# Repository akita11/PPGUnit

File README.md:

# PPG Clip

[M5Stack社の心拍センサユニット](https://www.switch-science.com/products/5695)と機能的に互換のUnitです。
光学脈波(PPG)センサのMAX30100を使用し、光学脈波やSpO2、そこから心拍数の計測ができます。
また[PPG Clip部品セット](https://github.com/akita11/PPGclip)と組み合わせることで、透過型PPG計測装置をつくることができます。

※センサICのMAX30100は、再生品を使用している場合があります。基本的な測定には問題がないことは確認済みですが、新品とは多少の性能の差異がある場合があります。

## 使い方

[M5Stack社の心拍センサユニット](https://www.switch-science.com/products/5695)と機能的に互換ですので、そちらのソフトウエア(Arduino用ライブラリ、UIFlow等)がそのまま使用できます。

## 作り方

2枚の基板を、向きをあわせて、2組の4pピンヘッダではんだ付けします。
ピンヘッダの足は十分に短くカットしてください。

## 補足情報(I2C信号線について)

MAX30100のI2C信号線の端子の絶対最大定格は6.0Vです。
I2C信号線のプルアップ抵抗はGroveコネクタのVDD側(M5Stackシリーズでは5V)に接続されており、HレベルはVDD電圧（同5V）となりますが、絶対最大定格を超えません。
M5Stack社の心拍センサユニットでは、ここに電圧変換用の部品が入っていますが、I2C信号の波形を観測したところ、立ち下がり速度がかなり遅く、特に400kHz通信の場合には通信エラーが多発する現象が確認されましたので、この構成としています。

## Author

Junichi Akita (@akita11) / akita@ifdl.jp

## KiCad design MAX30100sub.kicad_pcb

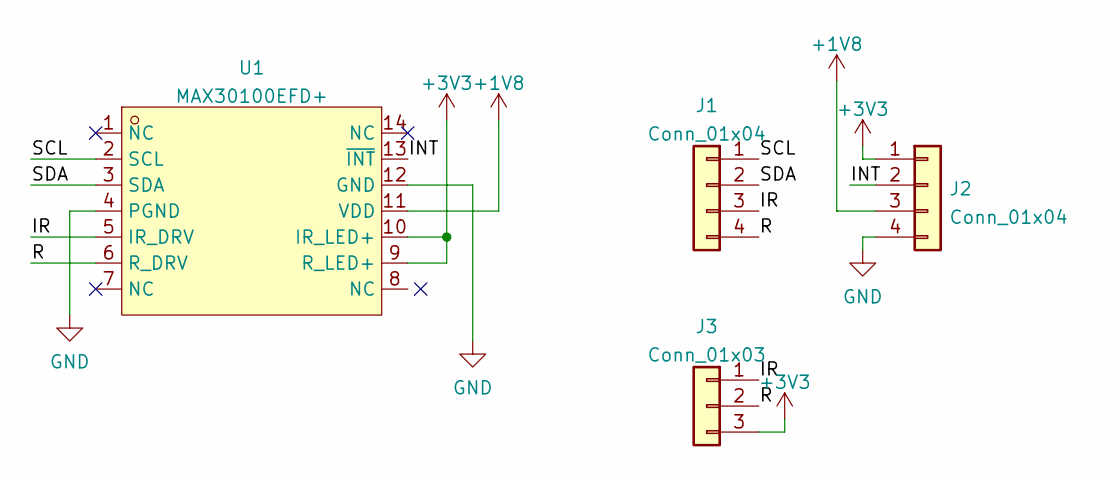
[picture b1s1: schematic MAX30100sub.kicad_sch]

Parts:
J1, J2: Conn_01x04; PinHeader_1x04_P2.54mm_Vertical
J3: Conn_01x03; PinSocket_1x03_P2.00mm_Vertical
U1: MAX30100EFD+; SENSOR-SMD_MAX30100EFD; LCSC Part C92512

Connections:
+1V8: J2.3, U1.11 (VDD)
+3V3: J2.1, J3.3, U1.9 (R_LED+), U1.10 (IR_LED+)
/INT: J2.2, U1.13 (~INT)
/IR: J1.3, J3.1, U1.5 (IR_DRV)
/R: J1.4, J3.2, U1.6 (R_DRV)
/SCL: J1.1, U1.2 (SCL)
/SDA: J1.2, U1.3 (SDA)
GND: J2.4, U1.4 (PGND), U1.12 (GND)

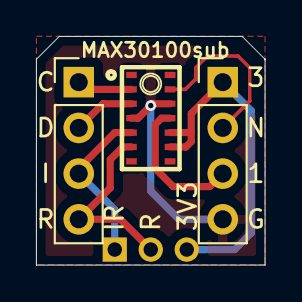
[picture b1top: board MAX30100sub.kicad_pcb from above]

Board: 2 copper layers, 12.7 x 12.7 mm, 4 parts (0 on the bottom side), 8 nets.

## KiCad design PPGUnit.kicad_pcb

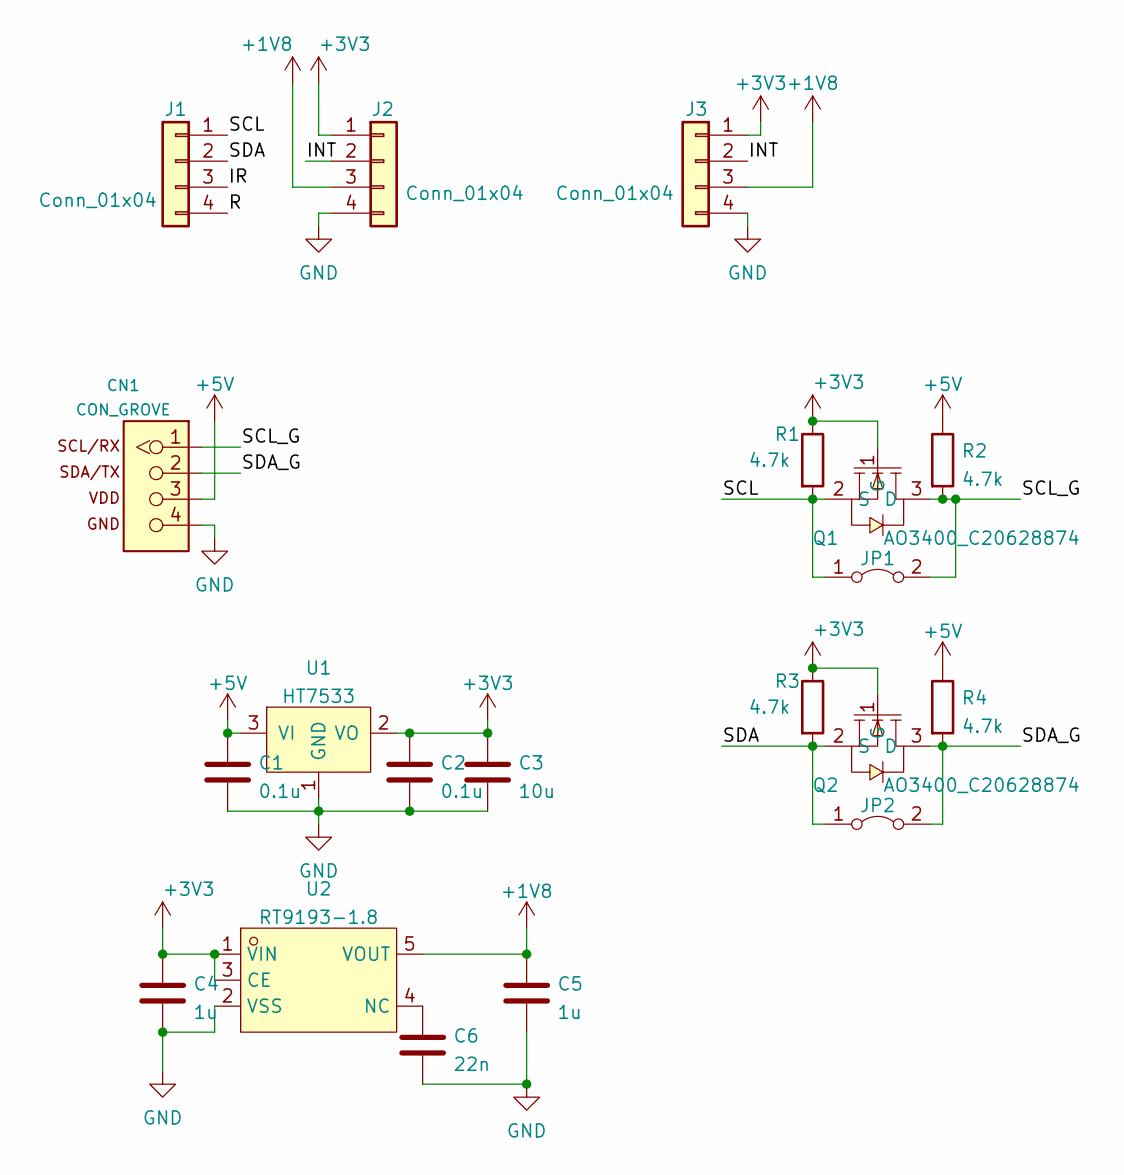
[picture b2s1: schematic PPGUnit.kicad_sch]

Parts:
C1, C2: 0.1u; C_0603_1608Metric
C3: 10u; C_0603_1608Metric
C4, C5: 1u; C_0603_1608Metric
C6: 22n; C_0603_1608Metric
CN1: CON_GROVE; CON_GROVE_H
J1, J2, J3: Conn_01x04; PinSocket_1x04_P2.54mm_Vertical
JP1, JP2: Jumper_2_Bridged; SolderJumper-2_P1.3mm_Bridged_Pad1.0x1.5mm
Q1, Q2: AO3400_C20628874; SOT-23-3_L2.9-W1.3-P1.90-LS2.4-BR; LCSC Part C20628874
R1, R2, R3, R4: 4.7k; R_0603_1608Metric
U1: HT7533; SOT-23
U2: RT9193-1.8; SOT-23-5_L2.9-W1.6-P0.95-LS2.8-BR; LCSC Part C22466424

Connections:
+1V8: C5.1, J2.3, J3.3, U2.5 (VOUT)
+3V3: C2.1, C3.1, C4.1, J2.1, J3.1, Q1.1 (G), Q2.1 (G), R1.1, R3.1, U1.2 (VO), U2.1 (VIN), U2.3 (CE)
+5V: C1.1, CN1.3, R2.1, R4.1, U1.3 (VI)
/INT: J2.2, J3.2
/IR: J1.3
/R: J1.4
/SCL: J1.1, JP1.1 (A), Q1.2 (S), R1.2
/SCL_G: CN1.1, JP1.2 (B), Q1.3 (D), R2.2
/SDA: J1.2, JP2.1 (A), Q2.2 (S), R3.2
/SDA_G: CN1.2, JP2.2 (B), Q2.3 (D), R4.2
GND: C1.2, C2.2, C3.2, C4.2, C5.2, C6.2, CN1.4, J2.4, J3.4, U1.1 (GND), U2.2 (VSS)
unnamed: C6.1, U2.4 (NC)

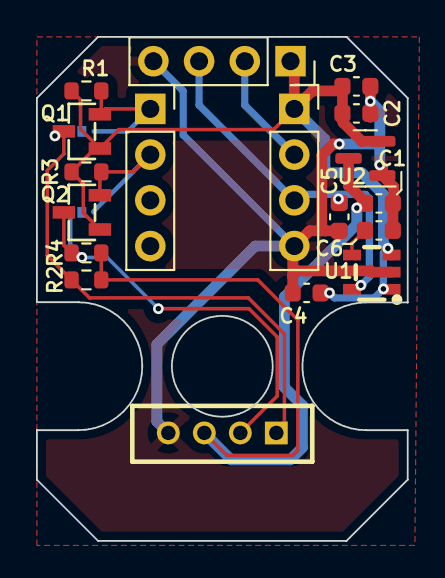
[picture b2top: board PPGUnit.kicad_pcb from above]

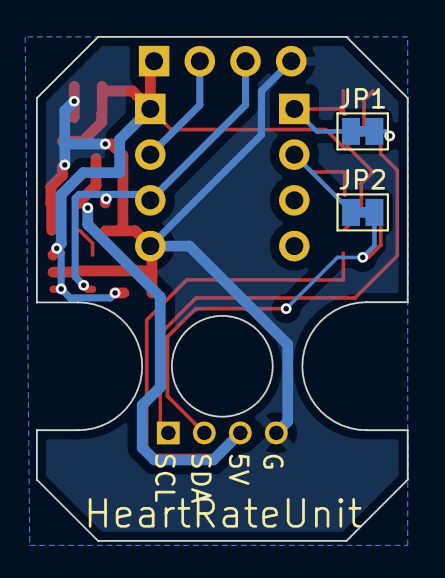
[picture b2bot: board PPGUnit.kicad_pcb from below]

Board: 2 copper layers, 20.6 x 28.0 mm, 20 parts (2 on the bottom side), 10 nets.

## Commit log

2026-01-28 initial commit (no photo)
2026-01-28 typo fix
2026-01-28 typo fix in URL
2026-01-28 add photo
2026-02-03 Fix typo in I2C signal line referene
